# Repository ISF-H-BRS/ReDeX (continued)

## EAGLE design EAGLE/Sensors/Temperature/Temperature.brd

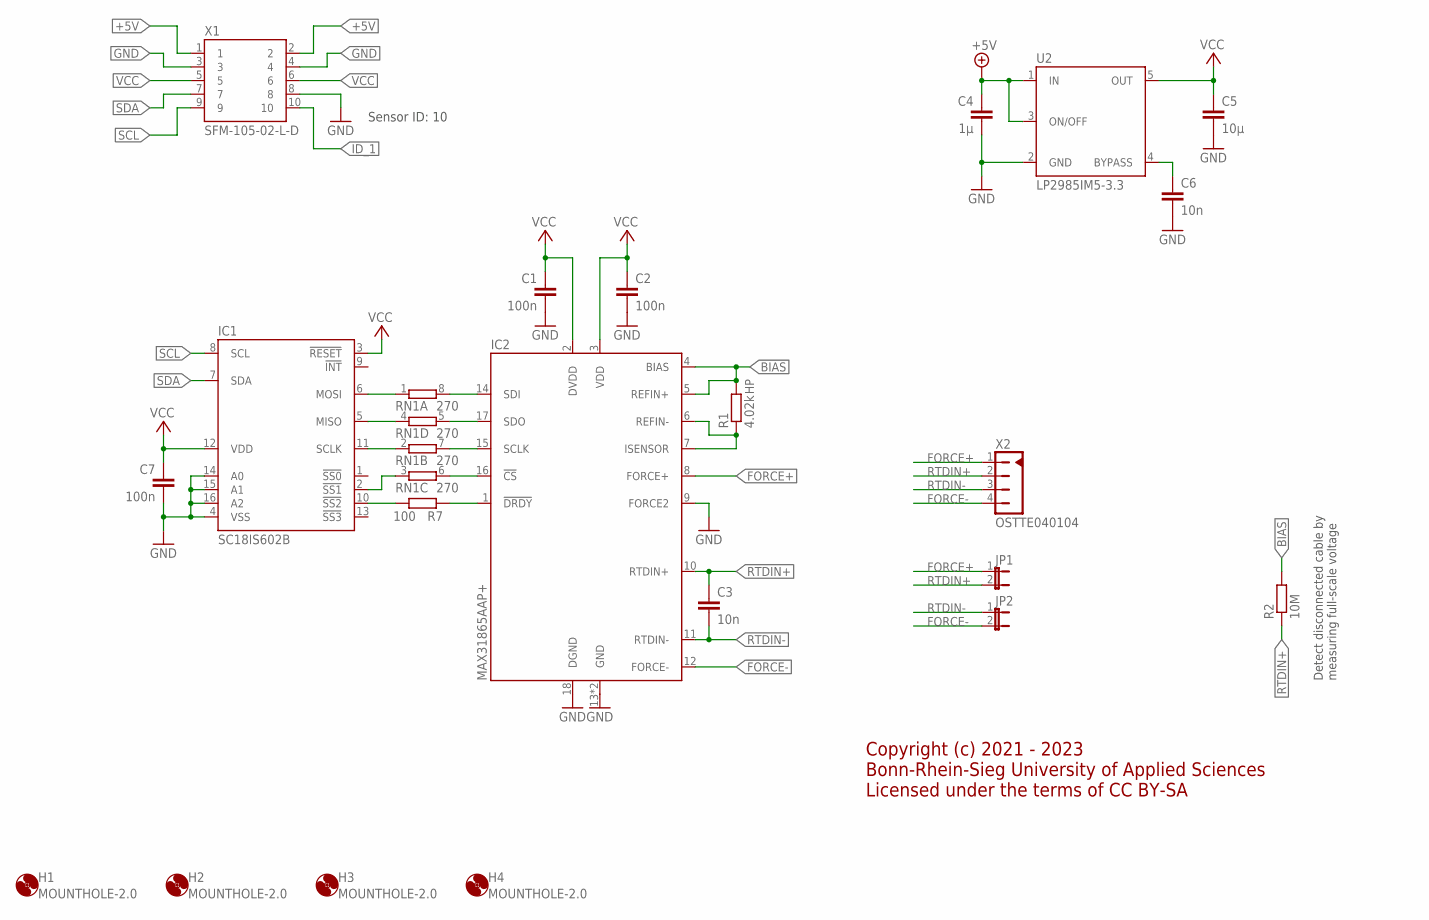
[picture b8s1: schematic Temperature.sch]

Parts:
C1, C2, C7: 100n; C0603
C3, C6: 10n; C0603
C4: 1µ; C0603
C5: 10µ; C0603
H1, H2, H3, H4: MOUNTHOLE-2.0; 2.0
IC1: SC18IS602B; TSSOP16
IC2: MAX31865AAP+; SSOP20
JP1, JP2: JP1E; JP1
R1: 4.02k; R0603
R2: 10M; R0603
R7: 100; R0603
RN1: 270; EXB38V
U2: LP2985IM5-3.3; SOT23-5
X1: SFM-105-02-L-D; SAMTEC-SFM-105-02-L-D
X2: OSTTE040104; OSTTE04

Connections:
+5V: C4.1, U2.1 (IN), U2.3 (ON/OFF), X1.1, X1.2
BIAS: IC2.4 (BIAS), IC2.5 (REFIN+), R1.2, R2.2
FORCE+: IC2.8 (FORCE+), JP1.1, X2.1
FORCE-: IC2.12 (FORCE-), JP2.2, X2.4
GND: C1.2, C2.2, C4.2, C5.2, C6.2, C7.2, IC1.4 (VSS), IC1.14 (A0), IC1.15 (A1), IC1.16 (A2), IC2.9 (FORCE2), IC2.13 (GND), IC2.18 (DGND), IC2.19 (GND), U2.2 (GND), X1.3, X1.4, X1.8
ID_1: X1.10
unnamed: IC1.10 (!SS2), R7.2
unnamed: IC2.16 (!CS), RN1.6 (2)
unnamed: IC2.15 (SCLK), RN1.7 (2)
unnamed: IC2.6 (REFIN-), IC2.7 (ISENSOR), R1.1
unnamed: IC2.17 (SDO), RN1.5 (2)
unnamed: IC2.14 (SDI), RN1.8 (2)
unnamed: IC1.6 (MOSI), RN1.1
unnamed: C6.1, U2.4 (BYPASS)
unnamed: IC1.5 (MISO), RN1.4 (1)
unnamed: IC1.11 (SCLK), RN1.2 (1)
unnamed: IC1.2 (!SS1), RN1.3 (1)
unnamed: IC2.1 (!DRDY), R7.1
RTDIN+: C3.1, IC2.10 (RTDIN+), JP1.2, R2.1, X2.2
RTDIN-: C3.2, IC2.11 (RTDIN-), JP2.1, X2.3
SCL: IC1.8 (SCL), X1.9
SDA: IC1.7 (SDA), X1.7
VCC: C1.1, C2.1, C5.1, C7.1, IC1.3 (!RESET), IC1.12 (VDD), IC2.2 (DVDD), IC2.3 (VDD), U2.5 (OUT), X1.5, X1.6

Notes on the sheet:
Detect disconnected cable by measuring full-scale voltage
Sensor ID: 10
Copyright (c) 2021 - 2023 Bonn-Rhein-Sieg University of Applied Sciences Licensed under the terms of CC BY-SA

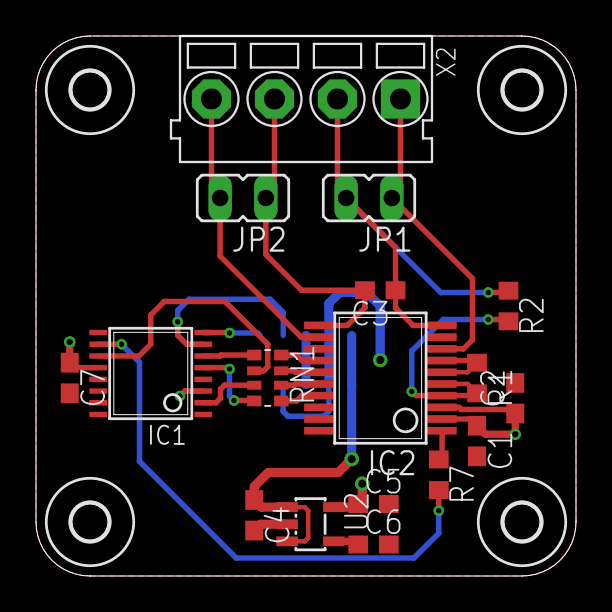
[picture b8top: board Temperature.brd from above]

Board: 2 copper layers, 30.0 x 30.0 mm, 22 parts (1 on the bottom side), 22 nets.

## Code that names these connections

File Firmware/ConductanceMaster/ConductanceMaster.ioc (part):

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Mcu.Name=STM32F446R(C-E)Tx
Mcu.Package=LQFP64
Mcu.UserName=STM32F446RCTx
PA0-WKUP.GPIOParameters=GPIO_Label
PA0-WKUP.GPIO_Label=BUS_VOLTAGE
PA0-WKUP.Signal=ADCx_IN0
PA1.GPIOParameters=GPIO_Label
PA1.GPIO_Label=BUS_CURRENT
PA1.Signal=ADCx_IN1
PA11.Mode=Device_Only
PA11.Signal=USB_OTG_FS_DM
PA12.Mode=Device_Only
PA12.Signal=USB_OTG_FS_DP
PA13.Mode=Serial_Wire
PA13.Signal=SYS_JTMS-SWDIO
PA14.Mode=Serial_Wire
PA14.Signal=SYS_JTCK-SWCLK
PA4.GPIOParameters=PinState,GPIO_Label
PA4.GPIO_Label=SLAVE2_CS
PA4.PinState=GPIO_PIN_SET
PA4.Signal=GPIO_Output
PA5.GPIOParameters=GPIO_Label
PA5.GPIO_Label=SLAVE2_SCK
PA5.Mode=Full_Duplex_Master
PA5.Signal=SPI1_SCK
PA6.GPIOParameters=GPIO_Label
PA6.GPIO_Label=SLAVE2_MISO
PA6.Mode=Full_Duplex_Master
PA6.Signal=SPI1_MISO
PA7.GPIOParameters=GPIO_Label
PA7.GPIO_Label=SLAVE2_MOSI
PA7.Mode=Full_Duplex_Master
PA7.Signal=SPI1_MOSI
PB12.GPIOParameters=PinState,GPIO_Label
PB12.GPIO_Label=SLAVE1_CS
PB12.PinState=GPIO_PIN_SET
PB12.Signal=GPIO_Output
PB13.GPIOParameters=GPIO_Label
PB13.GPIO_Label=SLAVE1_SCK
PB13.Mode=Full_Duplex_Master
PB13.Signal=SPI2_SCK
PB14.GPIOParameters=GPIO_Label
PB14.GPIO_Label=SLAVE1_MISO
PB14.Mode=Full_Duplex_Master
PB14.Signal=SPI2_MISO
PB15.GPIOParameters=GPIO_Label
PB15.GPIO_Label=SLAVE1_MOSI
PB15.Mode=Full_Duplex_Master
PB15.Signal=SPI2_MOSI
PB3.GPIOParameters=PinState,GPIO_PuPd,GPIO_Label,GPIO_ModeDefaultOutputPP
PB3.GPIO_Label=STATUS_BAD
PB3.GPIO_ModeDefaultOutputPP=GPIO_MODE_OUTPUT_OD
PB3.GPIO_PuPd=GPIO_NOPULL
PB3.PinState=GPIO_PIN_SET
PB3.Signal=GPIO_Output
PB4.GPIOParameters=PinState,GPIO_PuPd,GPIO_Label,GPIO_ModeDefaultOutputPP
PB4.GPIO_Label=STATUS_GOOD
PB4.GPIO_ModeDefaultOutputPP=GPIO_MODE_OUTPUT_OD
PB4.GPIO_PuPd=GPIO_NOPULL
PB4.PinState=GPIO_PIN_SET
PB4.Signal=GPIO_Output
PC11.GPIOParameters=GPIO_PuPd,GPIO_Label
PC11.GPIO_Label=VARIANT1
PC11.GPIO_PuPd=GPIO_PULLUP
PC11.Signal=GPIO_Input
PC12.GPIOParameters=GPIO_PuPd,GPIO_Label
PC12.GPIO_Label=VARIANT0
PC12.GPIO_PuPd=GPIO_PULLUP
PC12.Signal=GPIO_Input
PC4.GPIOParameters=GPIO_PuPd,GPIO_Label
PC4.GPIO_Label=SLAVE2_CON
PC4.GPIO_PuPd=GPIO_PULLUP
PC4.Signal=GPIO_Input
PC5.GPIOParameters=GPIO_PuPd,GPIO_Label
PC5.GPIO_Label=SLAVE2_DRDY
PC5.GPIO_PuPd=GPIO_PULLUP
PC5.Signal=GPIO_Input
PC6.GPIOParameters=GPIO_PuPd,GPIO_Label
PC6.GPIO_Label=SLAVE1_CON
PC6.GPIO_PuPd=GPIO_PULLUP
PC6.Signal=GPIO_Input
PC7.GPIOParameters=GPIO_PuPd,GPIO_Label
PC7.GPIO_Label=SLAVE1_DRDY
PC7.GPIO_PuPd=GPIO_PULLUP
PC7.Signal=GPIO_Input
PH0-OSC_IN.Mode=HSE-External-Clock-Source
PH0-OSC_IN.Signal=RCC_OSC_IN
PH1-OSC_OUT.Mode=HSE-External-Clock-Source
PH1-OSC_OUT.Signal=RCC_OSC_OUT
RCC.HSE_VALUE=16000000
RCC.SYSCLKFreq_VALUE=168000000
RCC.SYSCLKSource=RCC_SYSCLKSOURCE_PLLCLK
board=custom

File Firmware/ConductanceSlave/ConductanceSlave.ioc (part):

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Mcu.Name=STM32L552R(C-E)Tx
Mcu.Package=LQFP64
Mcu.UserName=STM32L552RCTx
PA13\ (JTMS/SWDIO).Mode=Serial_Wire
PA13\ (JTMS/SWDIO).Signal=DEBUG_JTMS-SWDIO
PA14\ (JTCK/SWCLK).Mode=Serial_Wire
PA14\ (JTCK/SWCLK).Signal=DEBUG_JTCK-SWCLK
PA15\ (JTDI).GPIOParameters=GPIO_PuPd,GPIO_Label
PA15\ (JTDI).GPIO_Label=VERSION_0
PA15\ (JTDI).GPIO_PuPd=GPIO_PULLDOWN
PA15\ (JTDI).Signal=GPIO_Input
PA2.GPIOParameters=GPIO_Label
PA2.GPIO_Label=CIN_FILTERED
PA2.Signal=ADCx_IN7
PA4.GPIOParameters=GPIO_Label
PA4.GPIO_Label=VZERO
PA4.Signal=COMP_DAC11_group
PA5.GPIOParameters=GPIO_Label
PA5.GPIO_Label=DAC_OUT
PA5.Signal=COMP_DAC12_group
PA6.GPIOParameters=GPIO_Label
PA6.GPIO_Label=VOUT
PA6.Mode=Follower
PA6.Signal=OPAMP2_VINP
PB0.GPIOParameters=GPIO_Label
PB0.GPIO_Label=VOUT_BUFFERED
PB0.Mode=Follower
PB0.Signal=OPAMP2_VOUT
PB10.GPIOParameters=GPIO_Speed,GPIO_Label
PB10.GPIO_Label=COMM_SCK
PB10.GPIO_Speed=GPIO_SPEED_FREQ_VERY_HIGH
PB10.Mode=Full_Duplex_Slave
PB10.Signal=SPI2_SCK
PB12.GPIOParameters=GPIO_PuPd,GPIO_Label,GPIO_ModeDefaultEXTI
PB12.GPIO_Label=COMM_CS
PB12.GPIO_ModeDefaultEXTI=GPIO_MODE_IT_RISING_FALLING
PB12.GPIO_PuPd=GPIO_PULLUP
PB12.Signal=GPXTI12
PB13.GPIOParameters=PinState,GPIO_PuPd,GPIO_Label,GPIO_ModeDefaultOutputPP
PB13.GPIO_Label=COMM_DRDY
PB13.GPIO_ModeDefaultOutputPP=GPIO_MODE_OUTPUT_OD
PB13.GPIO_PuPd=GPIO_NOPULL
PB13.PinState=GPIO_PIN_SET
PB13.Signal=GPIO_Output
PB14.GPIOParameters=GPIO_Speed,GPIO_Label
PB14.GPIO_Label=COMM_MISO
PB14.GPIO_Speed=GPIO_SPEED_FREQ_VERY_HIGH
PB14.Mode=Full_Duplex_Slave
PB14.Signal=SPI2_MISO
PB15.GPIOParameters=GPIO_Speed,GPIO_Label
PB15.GPIO_Label=COMM_MOSI
PB15.GPIO_Speed=GPIO_SPEED_FREQ_VERY_HIGH
PB15.Mode=Full_Duplex_Slave
PB15.Signal=SPI2_MOSI
PB3\ (JTDO/TRACESWO).GPIOParameters=GPIO_Label
PB3\ (JTDO/TRACESWO).GPIO_Label=MUX_A0
PB3\ (JTDO/TRACESWO).Signal=GPIO_Output
PB4\ (NJTRST).GPIOParameters=PinState,GPIO_PuPd,GPIO_Label,GPIO_ModeDefaultOutputPP
PB4\ (NJTRST).GPIO_Label=MUX_A1
PB4\ (NJTRST).GPIO_ModeDefaultOutputPP=GPIO_MODE_OUTPUT_PP
PB4\ (NJTRST).GPIO_PuPd=GPIO_NOPULL
PB4\ (NJTRST).PinState=GPIO_PIN_RESET
PB4\ (NJTRST).Signal=GPIO_Output
PB8.GPIOParameters=GPIO_Label
PB8.GPIO_Label=TESTOUT
PB8.Signal=GPIO_Output
PC10.GPIOParameters=GPIO_PuPd,GPIO_Label
PC10.GPIO_Label=VERSION_1
PC10.GPIO_PuPd=GPIO_PULLDOWN
PC10.Signal=GPIO_Input
PC11.GPIOParameters=PinState,GPIO_PuPd,GPIO_Label,GPIO_ModeDefaultOutputPP
PC11.GPIO_Label=STATUS_GOOD
PC11.GPIO_ModeDefaultOutputPP=GPIO_MODE_OUTPUT_OD
PC11.GPIO_PuPd=GPIO_NOPULL
PC11.PinState=GPIO_PIN_SET
PC11.Signal=GPIO_Output
PC12.GPIOParameters=PinState,GPIO_PuPd,GPIO_Label,GPIO_ModeDefaultOutputPP
PC12.GPIO_Label=STATUS_BAD
PC12.GPIO_ModeDefaultOutputPP=GPIO_MODE_OUTPUT_OD
PC12.GPIO_PuPd=GPIO_NOPULL
PC12.PinState=GPIO_PIN_SET
PC12.Signal=GPIO_Output
PC4.GPIOParameters=GPIO_Label
PC4.GPIO_Label=VOUT_FILTERED
PC4.Signal=ADCx_IN13
PC6.GPIOParameters=PinState,GPIO_PuPd,GPIO_Label,GPIO_ModeDefaultOutputPP
PC6.GPIO_Label=COMM_CON
PC6.GPIO_ModeDefaultOutputPP=GPIO_MODE_OUTPUT_OD
PC6.GPIO_PuPd=GPIO_NOPULL
PC6.PinState=GPIO_PIN_SET
PC6.Signal=GPIO_Output
PD2.GPIOParameters=GPIO_Label
PD2.GPIO_Label=MUX_EN
PD2.Signal=GPIO_Output
PH0-OSC_IN\ (PH0).Mode=HSE-External-Clock-Source
PH0-OSC_IN\ (PH0).Signal=RCC_OSC_IN
RCC.HSE_VALUE=16000000
RCC.SYSCLKFreq_VALUE=110000000
RCC.SYSCLKSource=RCC_SYSCLKSOURCE_PLLCLK
board=custom

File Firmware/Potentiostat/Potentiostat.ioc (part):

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Mcu.Name=STM32L412KBTx
Mcu.Package=LQFP32
Mcu.UserName=STM32L412KBTx
PA0-CK_IN.Mode=HSE-External-Clock-Source-for-LittleOrca
PA0-CK_IN.Signal=RCC_CK_IN
PA11.Mode=Device
PA11.Signal=USB_DM
PA12.Mode=Device
PA12.Signal=USB_DP
PA13\ (JTMS/SWDIO).Mode=Serial_Wire
PA13\ (JTMS/SWDIO).Signal=SYS_JTMS-SWDIO
PA14\ (JTCK/SWCLK).Mode=Serial_Wire
PA14\ (JTCK/SWCLK).Signal=SYS_JTCK-SWCLK
PA2.GPIOParameters=PinState,GPIO_PuPd,GPIO_Label,GPIO_ModeDefaultOutputPP
PA2.GPIO_Label=ADC_CONVST
PA2.GPIO_ModeDefaultOutputPP=GPIO_MODE_OUTPUT_OD
PA2.GPIO_PuPd=GPIO_PULLUP
PA2.PinState=GPIO_PIN_SET
PA2.Signal=GPIO_Output
PA3.GPIOParameters=PinState,GPIO_PuPd,GPIO_Label,GPIO_ModeDefaultOutputPP
PA3.GPIO_Label=ADC_CS1
PA3.GPIO_ModeDefaultOutputPP=GPIO_MODE_OUTPUT_OD
PA3.GPIO_PuPd=GPIO_NOPULL
PA3.PinState=GPIO_PIN_SET
PA3.Signal=GPIO_Output
PA4.GPIOParameters=PinState,GPIO_PuPd,GPIO_Label,GPIO_ModeDefaultOutputPP
PA4.GPIO_Label=ADC_CS2
PA4.GPIO_ModeDefaultOutputPP=GPIO_MODE_OUTPUT_OD
PA4.GPIO_PuPd=GPIO_NOPULL
PA4.PinState=GPIO_PIN_SET
PA4.Signal=GPIO_Output
PA5.GPIOParameters=GPIO_Speed,GPIO_Label
PA5.GPIO_Label=ADC_SCK
PA5.GPIO_Speed=GPIO_SPEED_FREQ_HIGH
PA5.Mode=RX_Only_Simplex_Unidirect_Master
PA5.Signal=SPI1_SCK
PA6.GPIOParameters=GPIO_Speed,GPIO_Label
PA6.GPIO_Label=ADC_MISO
PA6.GPIO_Speed=GPIO_SPEED_FREQ_HIGH
PA6.Mode=RX_Only_Simplex_Unidirect_Master
PA6.Signal=SPI1_MISO
PA7.GPIOParameters=PinState,GPIO_PuPd,GPIO_Label,GPIO_ModeDefaultOutputPP
PA7.GPIO_Label=DAC_AUX
PA7.GPIO_ModeDefaultOutputPP=GPIO_MODE_OUTPUT_OD
PA7.GPIO_PuPd=GPIO_PULLUP
PA7.PinState=GPIO_PIN_SET
PA7.Signal=GPIO_Output
PA8.GPIOParameters=PinState,GPIO_PuPd,GPIO_Label,GPIO_ModeDefaultOutputPP
PA8.GPIO_Label=OUTPUT_ENABLE
PA8.GPIO_ModeDefaultOutputPP=GPIO_MODE_OUTPUT_OD
PA8.GPIO_PuPd=GPIO_NOPULL
PA8.PinState=GPIO_PIN_SET
PA8.Signal=GPIO_Output
PB0.GPIOParameters=PinState,GPIO_PuPd,GPIO_Label,GPIO_ModeDefaultOutputPP
PB0.GPIO_Label=STATUS_GOOD
PB0.GPIO_ModeDefaultOutputPP=GPIO_MODE_OUTPUT_OD
PB0.GPIO_PuPd=GPIO_NOPULL
PB0.PinState=GPIO_PIN_SET
PB0.Signal=GPIO_Output
PB1.GPIOParameters=PinState,GPIO_PuPd,GPIO_Label,GPIO_ModeDefaultOutputPP
PB1.GPIO_Label=STATUS_BAD
PB1.GPIO_ModeDefaultOutputPP=GPIO_MODE_OUTPUT_OD
PB1.GPIO_PuPd=GPIO_NOPULL
PB1.PinState=GPIO_PIN_SET
PB1.Signal=GPIO_Output
PB3\ (JTDO/TRACESWO).GPIOParameters=GPIO_Label
PB3\ (JTDO/TRACESWO).GPIO_Label=MUX_A0
PB3\ (JTDO/TRACESWO).Signal=GPIO_Output
PB4\ (NJTRST).GPIOParameters=GPIO_Label
PB4\ (NJTRST).GPIO_Label=MUX_A1
PB4\ (NJTRST).Signal=GPIO_Output
PB5.GPIOParameters=PinState,GPIO_PuPd,GPIO_Label,GPIO_ModeDefaultOutputPP
PB5.GPIO_Label=MUX_EN
PB5.GPIO_ModeDefaultOutputPP=GPIO_MODE_OUTPUT_OD
PB5.GPIO_PuPd=GPIO_NOPULL
PB5.PinState=GPIO_PIN_SET
PB5.Signal=GPIO_Output
PB6.GPIOParameters=GPIO_Speed,GPIO_Label
PB6.GPIO_Label=SCL
PB6.GPIO_Speed=GPIO_SPEED_FREQ_MEDIUM
PB6.Mode=I2C
PB6.Signal=I2C1_SCL
PB7.GPIOParameters=GPIO_Speed,GPIO_Label
PB7.GPIO_Label=SDA
PB7.GPIO_Speed=GPIO_SPEED_FREQ_MEDIUM
PB7.Mode=I2C
PB7.Signal=I2C1_SDA
PC14-OSC32_IN\ (PC14).GPIOParameters=PinState,GPIO_Label
PC14-OSC32_IN\ (PC14).GPIO_Label=PWR_ENABLE
PC14-OSC32_IN\ (PC14).PinState=GPIO_PIN_SET
PC14-OSC32_IN\ (PC14).Signal=GPIO_Output
RCC.HSE_VALUE=16000000
RCC.SYSCLKFreq_VALUE=80000000
RCC.SYSCLKSource=RCC_SYSCLKSOURCE_PLLCLK
board=custom

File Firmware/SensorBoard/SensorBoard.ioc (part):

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Mcu.Name=STM32L412KBTx
Mcu.Package=LQFP32
Mcu.UserName=STM32L412KBTx
PA0-CK_IN.GPIOParameters=GPIO_Label
PA0-CK_IN.GPIO_Label=BUS_VOLTAGE
PA0-CK_IN.Mode=Follower
PA0-CK_IN.Signal=OPAMP1_VINP
PA1.GPIOParameters=GPIO_Label
PA1.GPIO_Label=BUS_CURRENT
PA1.Signal=ADCx_IN6
PA11.Mode=Device
PA11.Signal=USB_DM
PA12.Mode=Device
PA12.Signal=USB_DP
PA13\ (JTMS/SWDIO).Mode=Serial_Wire
PA13\ (JTMS/SWDIO).Signal=SYS_JTMS-SWDIO
PA14\ (JTCK/SWCLK).Mode=Serial_Wire
PA14\ (JTCK/SWCLK).Signal=SYS_JTCK-SWCLK
PA15\ (JTDI).GPIOParameters=PinState,GPIO_PuPd,GPIO_Label,GPIO_ModeDefaultOutputPP
PA15\ (JTDI).GPIO_Label=STATUS_GOOD
PA15\ (JTDI).GPIO_ModeDefaultOutputPP=GPIO_MODE_OUTPUT_OD
PA15\ (JTDI).GPIO_PuPd=GPIO_NOPULL
PA15\ (JTDI).PinState=GPIO_PIN_SET
PA15\ (JTDI).Signal=GPIO_Output
PA3.GPIOParameters=GPIO_Label
PA3.GPIO_Label=BUS_VOLTAGE_AMPLIFIED
PA3.Mode=Follower
PA3.Signal=OPAMP1_VOUT
PA4.GPIOParameters=GPIO_PuPd,GPIO_Label
PA4.GPIO_Label=ID1_0
PA4.GPIO_PuPd=GPIO_NOPULL
PA4.Signal=GPIO_Input
PA5.GPIOParameters=GPIO_PuPd,GPIO_Label
PA5.GPIO_Label=ID1_1
PA5.GPIO_PuPd=GPIO_NOPULL
PA5.Signal=GPIO_Input
PA7.GPIOParameters=GPIO_Label
PA7.GPIO_Label=SCL1
PA7.Mode=I2C
PA7.Signal=I2C3_SCL
PB0.GPIOParameters=GPIO_PuPd,GPIO_Label
PB0.GPIO_Label=VARIANT0
PB0.GPIO_PuPd=GPIO_PULLUP
PB0.Signal=GPIO_Input
PB1.GPIOParameters=GPIO_PuPd,GPIO_Label
PB1.GPIO_Label=VARIANT1
PB1.GPIO_PuPd=GPIO_PULLUP
PB1.Signal=GPIO_Input
PB3\ (JTDO/TRACESWO).GPIOParameters=PinState,GPIO_PuPd,GPIO_Label,GPIO_ModeDefaultOutputPP
PB3\ (JTDO/TRACESWO).GPIO_Label=STATUS_BAD
PB3\ (JTDO/TRACESWO).GPIO_ModeDefaultOutputPP=GPIO_MODE_OUTPUT_OD
PB3\ (JTDO/TRACESWO).GPIO_PuPd=GPIO_NOPULL
PB3\ (JTDO/TRACESWO).PinState=GPIO_PIN_SET
PB3\ (JTDO/TRACESWO).Signal=GPIO_Output
PB4\ (NJTRST).GPIOParameters=GPIO_Label
PB4\ (NJTRST).GPIO_Label=SDA1
PB4\ (NJTRST).Mode=I2C
PB4\ (NJTRST).Signal=I2C3_SDA
PB6.GPIOParameters=GPIO_Label
PB6.GPIO_Label=SCL2
PB6.Mode=I2C
PB6.Signal=I2C1_SCL
PB7.GPIOParameters=GPIO_Label
PB7.GPIO_Label=SDA2
PB7.Mode=I2C
PB7.Signal=I2C1_SDA
PC14-OSC32_IN\ (PC14).GPIOParameters=GPIO_PuPd,GPIO_Label
PC14-OSC32_IN\ (PC14).GPIO_Label=ID2_0
PC14-OSC32_IN\ (PC14).GPIO_PuPd=GPIO_NOPULL
PC14-OSC32_IN\ (PC14).Signal=GPIO_Input
PC15-OSC32_OUT\ (PC15).GPIOParameters=GPIO_PuPd,GPIO_Label
PC15-OSC32_OUT\ (PC15).GPIO_Label=ID2_1
PC15-OSC32_OUT\ (PC15).GPIO_PuPd=GPIO_NOPULL
PC15-OSC32_OUT\ (PC15).Signal=GPIO_Input
RCC.HSE_VALUE=8000000
RCC.SYSCLKFreq_VALUE=80000000
RCC.SYSCLKSource=RCC_SYSCLKSOURCE_PLLCLK
board=custom

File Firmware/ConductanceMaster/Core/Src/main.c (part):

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  __HAL_RCC_GPIOD_CLK_ENABLE();

  /*Configure GPIO pin Output Level */
  HAL_GPIO_WritePin(SLAVE2_CS_GPIO_Port, SLAVE2_CS_Pin, GPIO_PIN_SET);

  /*Configure GPIO pin Output Level */
  HAL_GPIO_WritePin(GPIOB, SLAVE1_CS_Pin|STATUS_BAD_Pin|STATUS_GOOD_Pin, GPIO_PIN_SET);

  /*Configure GPIO pins : PC13 PC14 PC15 PC0
                           PC1 PC2 PC3 PC8
                           PC9 PC10 */
  GPIO_InitStruct.Pin = GPIO_PIN_13|GPIO_PIN_14|GPIO_PIN_15|GPIO_PIN_0
                          |GPIO_PIN_1|GPIO_PIN_2|GPIO_PIN_3|GPIO_PIN_8
                          |GPIO_PIN_9|GPIO_PIN_10;
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  GPIO_InitStruct.Pull = GPIO_NOPULL;
  HAL_GPIO_Init(GPIOC, &GPIO_InitStruct);

  /*Configure GPIO pins : PA2 PA3 PA8 PA9
                           PA10 PA15 */
  GPIO_InitStruct.Pin = GPIO_PIN_2|GPIO_PIN_3|GPIO_PIN_8|GPIO_PIN_9
                          |GPIO_PIN_10|GPIO_PIN_15;
  GPIO_InitStruct.Mode = GPIO_MODE_ANALOG;
  GPIO_InitStruct.Pull = GPIO_NOPULL;
  HAL_GPIO_Init(GPIOA, &GPIO_InitStruct);

  /*Configure GPIO pin : SLAVE2_CS_Pin */
  GPIO_InitStruct.Pin = SLAVE2_CS_Pin;
  GPIO_InitStruct.Mode = GPIO_MODE_OUTPUT_PP;
  GPIO_InitStruct.Pull = GPIO_NOPULL;
  GPIO_InitStruct.Speed = GPIO_SPEED_FREQ_LOW;
  HAL_GPIO_Init(SLAVE2_CS_GPIO_Port, &GPIO_InitStruct);

  /*Configure GPIO pins : SLAVE2_CON_Pin SLAVE2_DRDY_Pin SLAVE1_CON_Pin SLAVE1_DRDY_Pin
                           VARIANT1_Pin VARIANT0_Pin */
  GPIO_InitStruct.Pin = SLAVE2_CON_Pin|SLAVE2_DRDY_Pin|SLAVE1_CON_Pin|SLAVE1_DRDY_Pin
                          |VARIANT1_Pin|VARIANT0_Pin;
  GPIO_InitStruct.Mode = GPIO_MODE_INPUT;
  GPIO_InitStruct.Pull = GPIO_PULLUP;
  HAL_GPIO_Init(GPIOC, &GPIO_InitStruct);

  /*Configure GPIO pins : PB0 PB1 PB2 PB10
                           PB5 PB6 PB7 PB8
                           PB9 */
  GPIO_InitStruct.Pin = GPIO_PIN_0|GPIO_PIN_1|GPIO_PIN_2|GPIO_PIN_10
                          |GPIO_PIN_5|GPIO_PIN_6|GPIO_PIN_7|GPIO_PIN_8
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  GPIO_InitStruct.Pull = GPIO_NOPULL;
  HAL_GPIO_Init(GPIOB, &GPIO_InitStruct);

  /*Configure GPIO pin : SLAVE1_CS_Pin */
  GPIO_InitStruct.Pin = SLAVE1_CS_Pin;
  GPIO_InitStruct.Mode = GPIO_MODE_OUTPUT_PP;
  GPIO_InitStruct.Pull = GPIO_NOPULL;
  GPIO_InitStruct.Speed = GPIO_SPEED_FREQ_LOW;
  HAL_GPIO_Init(SLAVE1_CS_GPIO_Port, &GPIO_InitStruct);

  /*Configure GPIO pin : PD2 */
  GPIO_InitStruct.Pin = GPIO_PIN_2;
  GPIO_InitStruct.Mode = GPIO_MODE_ANALOG;
  GPIO_InitStruct.Pull = GPIO_NOPULL;
  HAL_GPIO_Init(GPIOD, &GPIO_InitStruct);

  /*Configure GPIO pins : STATUS_BAD_Pin STATUS_GOOD_Pin */
  GPIO_InitStruct.Pin = STATUS_BAD_Pin|STATUS_GOOD_Pin;
  GPIO_InitStruct.Mode = GPIO_MODE_OUTPUT_OD;
  GPIO_InitStruct.Pull = GPIO_NOPULL;
  GPIO_InitStruct.Speed = GPIO_SPEED_FREQ_LOW;
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
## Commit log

2024-01-07 Initial release.
